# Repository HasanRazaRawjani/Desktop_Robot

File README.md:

# Voxia

**Voxia** is a small desktop study companion robot. It sits on your desk with an animated face, can sense motion, move with servo “legs,” and — once the Pi build is fully wired — talk, listen, play music, and help you stay focused while you study.

## Why it exists

Voxia is meant to make studying less lonely and a bit more accountable. The long-term idea is a robot that:

- Keeps you company at the desk with a face on a small TFT
- Lets you **talk to it** (mic in, speaker out)
- **Plays music** while you work
- Uses a **USB camera** for simple awareness at the desk
- Helps **track where your phone is** — and if it detects the phone is in your hand when you should be studying, it can **start beeping** to nudge you to put it down
- Can **move** a little (servos) so it feels present, not like a static gadget

None of that is fully finished yet. The goal is a Pi-powered desk robot that can grow into those features over time.

## Current approach: Raspberry Pi 4 + breadboard

Will attach webcam and speakers externally and connect with Raspberry Pi ports by gluing them on the 3d printed case.

Early on, this project included a custom **ESP32 body PCB** in KiCad (socketed DevKit, ST7789 face display, MPU6050). That work was useful for learning PCB design, but the plan changed.

**Why the switch:** getting a full custom board fabbed and revised for every new idea (camera, mic, speaker, phone nudges, movement) was going to slow everything down. Wiring on a **Raspberry Pi 4** with **breadboards** makes it faster to try sensors, audio, and camera ideas before committing to another PCB.

So for now:

- **Brain:** Raspberry Pi 4  
- **Prototyping:** breadboards + jumper wires  
- **Display / IMU / servos / audio / camera:** added as modules as the build grows  

## (Not in use anymore) PCB work (still in the repo)
Note: I was gonna do a pcb for this project and I fully made one in kiKad too, but then I realized its not needed and it would be a waste of money and time to get one because then I would have to buy a soldering iron too.

The KiCad files are kept as a record of that first design pass:

| Path | Contents |
|------|----------|
| `esp32-body_PCBcad/` | KiCad project, footprints, and CAD helpers |
| `esp32-body_PCBcad/pcb and schematic/` | `esp32-body.kicad_pro` / `.kicad_sch` / `.kicad_pcb` |
| `esp32-body_PCBcad/pcb and schematic screenshots/` | Layout screenshots from the PCB sessions |

That board targeted an ESP32 DevKit V1, ST7789 TFT (face), and MPU6050 on female headers. It is **not** the active build path anymore, but it stays here for reference.

## Planned Pi peripherals

| Piece | Role |
|-------|------|
| TFT (ST7789) | Animated face / status UI |
| MPU6050 | Motion / orientation sensing |
| Servos | Small “leg” or body movement |
| USB camera | Desk awareness / study context |
| Mic | Voice input — talk to Voxia |
| Speaker | Voice replies, music, phone-nudge beeps |

## Journal

Build notes  in [`JOURNAL.md`](JOURNAL.md).

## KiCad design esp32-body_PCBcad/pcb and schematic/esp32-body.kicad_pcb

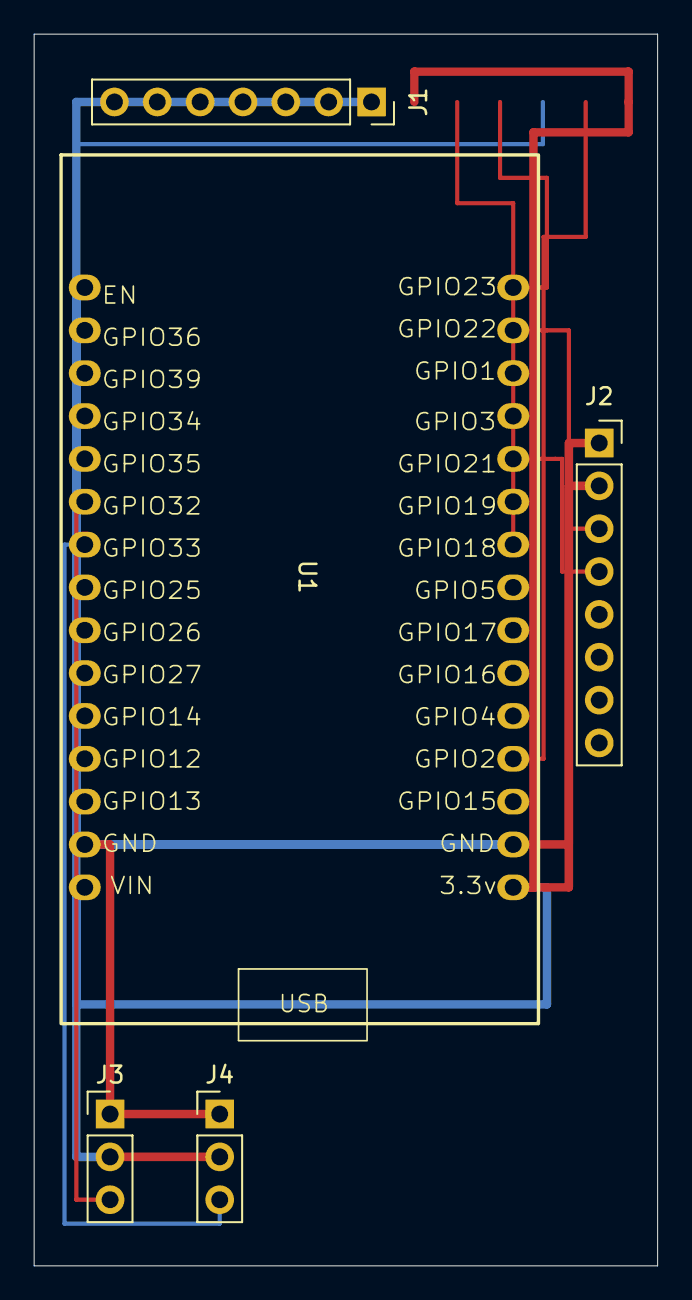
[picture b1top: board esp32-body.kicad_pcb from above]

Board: 2 copper layers, 37.0 x 73.0 mm, 5 parts (0 on the bottom side), 11 nets.

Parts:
J1: ST7789_TFT; PinSocket_1x07_P2.54mm_Vertical
J2: MPU6050; PinSocket_1x08_P2.54mm_Vertical
J3: SERVO1; PinHeader_1x03_P2.54mm_Vertical
J4: SERVO2; PinHeader_1x03_P2.54mm_Vertical
U1: ESP32_SOCKET_2x15; ESP32_30pin

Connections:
+3.3V: J1.2, J1.7, J2.1, U1.15 (EN), U1.16 (3.3v)
+5V: J3.2, J4.2, U1.1 (VIN)
/I2C_SCL: J2.3, U1.29 (GPIO22)
/I2C_SDA: J2.4, U1.26 (GPIO21)
/SERVO1: J3.3, U1.10 (GPIO32)
/SERVO2: J4.3, U1.9 (GPIO33)
/TFT_DC: J1.6, U1.19 (GPIO2)
/TFT_MOSI: J1.4, U1.30 (GPIO23)
/TFT_RST: J1.5, U1.6 (GPIO27)
/TFT_SCK: J1.3, U1.24 (GPIO18)
GND: J1.1, J2.2, J3.1, J4.1, U1.2 (GND), U1.17 (GND)

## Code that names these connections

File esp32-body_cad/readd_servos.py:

"""Re-add J3/J4 servo male headers + routes. Safe for KiCad name-based nets."""
from __future__ import annotations

import re
import uuid
from pathlib import Path

PCB = Path(
    r"c:\Users\rawja\OneDrive\Desktop\Desktop_Robot\esp32-body_cad\pcb and schematic\esp32-body.kicad_pcb"
)
BACKUP = PCB.with_suffix(".kicad_pcb.bak_before_servos")


def uid() -> str:
    return str(uuid.uuid4())


def seg(net: str, a, b, w: float, layer: str) -> str:
    return (
        f"\t(segment\n"
        f"\t\t(start {a[0]} {a[1]})\n"
        f"\t\t(end {b[0]} {b[1]})\n"
        f"\t\t(width {w})\n"
        f"\t\t(layer \"{layer}\")\n"
        f"\t\t(net \"{net}\")\n"
        f"\t\t(uuid \"{uid()}\")\n"
        f"\t)"
    )


def path(net: str, pts, w: float, layer: str) -> list[str]:
    out = []
    for a, b in zip(pts, pts[1:]):
        if a != b:
            out.append(seg(net, a, b, w, layer))
    return out


def header_fp(ref: str, value: str, path_uuid: str, x: float, y: float, nets: list[str]) -> str:
    pads = []
    shapes = ["rect", "oval", "oval"]
    for i, (net, shape) in enumerate(zip(nets, shapes), start=1):
        py = (i - 1) * 2.54
        pads.append(
            f'''\t\t(pad "{i}" thru_hole {shape}
\t\t\t(at 0 {py})
\t\t\t(size 1.7 1.7)
\t\t\t(drill 1)
\t\t\t(layers "*.Cu" "*.Mask")
\t\t\t(remove_unused_layers no)
\t\t\t(net "{net}")
\t\t\t(pintype "passive")
\t\t\t(uuid "{uid()}")
\t\t)'''
        )
    pads_txt = "\n".join(pads)
    return f'''\t(footprint "Connector_PinHeader_2.54mm:PinHeader_1x03_P2.54mm_Vertical"
\t\t(layer "F.Cu")
\t\t(uuid "{uid()}")
\t\t(at {x} {y})
\t\t(descr "Through hole straight pin header, 1x03, 2.54mm pitch, single row")
\t\t(tags "Through hole pin header THT 1x03 2.54mm single row")
\t\t(path "/{path_uuid}")
\t\t(sheetname "/")
\t\t(sheetfile "esp32-body.kicad_sch")
\t\t(property "Reference" "{ref}"
\t\t\t(at 0 -2.33)
\t\t\t(layer "F.SilkS")
\t\t\t(uuid "{uid()}")
\t\t\t(effects
\t\t\t\t(font
\t\t\t\t\t(size 1 1)
\t\t\t\t\t(thickness 0.15)
\t\t\t\t)
\t\t\t)
\t\t)
\t\t(property "Value" "{value}"
\t\t\t(at 0 7.41)
\t\t\t(layer "F.Fab")
\t\t\t(uuid "{uid()}")
\t\t\t(effects
\t\t\t\t(font
\t\t\t\t\t(size 1 1)
\t\t\t\t\t(thickness 0.15)
\t\t\t\t)
\t\t\t)
\t\t)
\t\t(attr through_hole)
\t\t(fp_line
\t\t\t(start -1.33 1.27)
\t\t\t(end -1.33 6.41)
\t\t\t(stroke (width 0.12) (type solid))
\t\t\t(layer "F.SilkS")
\t\t\t(uuid "{uid()}")
\t\t)
\t\t(fp_line
\t\t\t(start -1.33 1.27)
\t\t\t(end 1.33 1.27)
\t\t\t(stroke (width 0.12) (type solid))
\t\t\t(layer "F.SilkS")
\t\t\t(uuid "{uid()}")
\t\t)
\t\t(fp_line
\t\t\t(start -1.33 6.41)
\t\t\t(end 1.33 6.41)
\t\t\t(stroke (width 0.12) (type solid))
\t\t\t(layer "F.SilkS")
\t\t\t(uuid "{uid()}")
\t\t)
\t\t(fp_line
\t\t\t(start 1.33 1.27)
\t\t\t(end 1.33 6.41)
\t\t\t(stroke (width 0.12) (type solid))
\t\t\t(layer "F.SilkS")
\t\t\t(uuid "{uid()}")
\t\t)
\t\t(fp_line
\t\t\t(start -1.33 0)
\t\t\t(end -1.33 -1.33)
\t\t\t(stroke (width 0.12) (type solid))
\t\t\t(layer "F.SilkS")
\t\t\t(uuid "{uid()}")
\t\t)
\t\t(fp_line
\t\t\t(start -1.33 -1.33)
\t\t\t(end 0 -1.33)
\t\t\t(stroke (width 0.12) (type solid))
\t\t\t(layer "F.SilkS")
\t\t\t(uuid "{uid()}")
\t\t)
\t\t(fp_rect
\t\t\t(start -1.8 -1.8)
\t\t\t(end 1.8 6.85)
\t\t\t(stroke (width 0.05) (type default))
\t\t\t(fill no)
\t\t\t(layer "F.CrtYd")
\t\t\t(uuid "{uid()}")
\t\t)
{pads_txt}
\t\t(embedded_fonts no)
\t\t(model "${{KICAD10_3DMODEL_DIR}}/Connector_PinHeader_2.54mm.3dshapes/PinHeader_1x03_P2.54mm_Vertical.step"
\t\t\t(offset (xyz 0 0 0))
\t\t\t(scale (xyz 1 1 1))
\t\t\t(rotate (xyz 0 0 0))
\t\t)
\t)
'''


text = PCB.read_text(encoding="utf-8")
BACKUP.write_text(text, encoding="utf-8")
print("Backup:", BACKUP)

# Remove old PinHeader_1x03 if any
text = re.sub(
    r'\t\(footprint "Connector_PinHeader_2.54mm:PinHeader_1x03_P2.54mm_Vertical"[\s\S]*?\n\t\)\n',
    "",
    text,
)

# Assign U1 nets
for old, new in [
    ('(net "unconnected-(U1-VIN-Pad1)")', '(net "+5V")'),
    ('(net "unconnected-(U1-GPIO33-Pad9)")', '(net "/SERVO2")'),
    ('(net "unconnected-(U1-GPIO32-Pad10)")', '(net "/SERVO1")'),
    ('(net "unconnected-(U1-GND-Pad17)")', '(net "GND")'),
]:
    if old in text:
        text = text.replace(old, new, 1)
        print("pad net:", new)
    elif new in text:
        print("already:", new)
    else:
        print("WARN missing:", old)

J3 = (158.5, 91.0)
J4 = (165.0, 91.0)
fps = header_fp(
    "J3", "SERVO1", "af634168-65ad-4845-8390-6b38a8128340", *J3, ["GND", "+5V", "/SERVO1"]
)
fps += header_fp(
    "J4", "SERVO2", "d330271a-3ffe-4c54-81fb-b5e1a28daf97", *J4, ["GND", "+5V", "/SERVO2"]
)

edge = "\t(gr_rect\n\t\t(start 154 38.980514)"
if edge not in text:
    raise SystemExit("Edge.Cuts not found")
text = text.replace(edge, fps + edge, 1)

# Remove previous servo routes
for net in ("/SERVO1", "/SERVO2", "+5V"):
    text = re.sub(
        rf"\t\(segment\n"
        rf"\t\t\(start [^\n]+\)\n"
        rf"\t\t\(end [^\n]+\)\n"
        rf"\t\t\(width [^\n]+\)\n"
        rf"\t\t\(layer \"[^\"]+\"\)\n"
        rf"\t\t\(net \"{re.escape(net)}\"\)\n"
        rf"\t\t\(uuid \"[^\"]+\"\)\n"
        rf"\t\)\n?",
        "",
        text,
    )

j3 = {1: (J3[0], J3[1]), 2: (J3[0], J3[1] + 2.54), 3: (J3[0], J3[1] + 5.08)}
j4 = {1: (J4[0], J4[1]), 2: (J4[0], J4[1] + 2.54), 3: (J4[0], J4[1] + 5.08)}
u1_10, u1_9, u1_1, u1_2, u1_17 = (
    (157.0, 66.7),
    (157.0, 69.24),
    (157.0, 89.56),
    (157.0, 87.02),
    (182.4, 87.02),
)

items: list[str] = []
SIG, PWR = 0.25, 0.5
items += path("/SERVO1", [u1_10, (156.5, u1_10[1]), (156.5, j3[3][1]), j3[3]], SIG, "F.Cu")
items += path(
    "/SERVO2",
    [u1_9, (155.8, u1_9[1]), (155.8, 97.5), (j4[3][0], 97.5), j4[3]],
    SIG,
    "B.Cu",
)
items += path("GND", [j3[1], (j3[1][0], u1_2[1]), u1_2], PWR, "F.Cu")
items += path("GND", [j4[1], (j3[1][0], j4[1][1]), j3[1]], PWR, "F.Cu")
# only add U1.17 GND if not already connected somehow - additive is fine
items += path("GND", [u1_17, u1_2], PWR, "B.Cu")
items += path("+5V", [u1_1, (156.5, u1_1[1]), (156.5, j3[2][1]), j3[2]], PWR, "B.Cu")
items += path("+5V", [j3[2], (j4[2][0], j3[2][1]), j4[2]], PWR, "F.Cu")

# Insert segments before final embedded_fonts / )
text = re.sub(r"\n\t\(embedded_fonts no\)\n\)\s*\Z", "\n", text)
text = text.rstrip() + "\n" + "\n".join(items) + "\n\t(embedded_fonts no)\n)\n"

PCB.write_text(text, encoding="utf-8")

final = PCB.read_text(encoding="utf-8")
print("J3:", '(property "Reference" "J3"' in final)
print("J4:", '(property "Reference" "J4"' in final)
print("SERVO1 refs:", final.count('"/SERVO1"'))
print("SERVO2 refs:", final.count('"/SERVO2"'))
print("+5V refs:", final.count('"+5V"'))
print("segments:", final.count("(segment"))
print("OK — close KiCad WITHOUT saving, then reopen this file")
